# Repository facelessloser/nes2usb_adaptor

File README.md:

# nes2usb_adaptor
NES to USB adaptor

Blog post - https://facelesstech.wordpress.com/2017/03/26/nes-to-usb-adaptor-fail/
Youtube - https://youtu.be/qgFyICQwugc

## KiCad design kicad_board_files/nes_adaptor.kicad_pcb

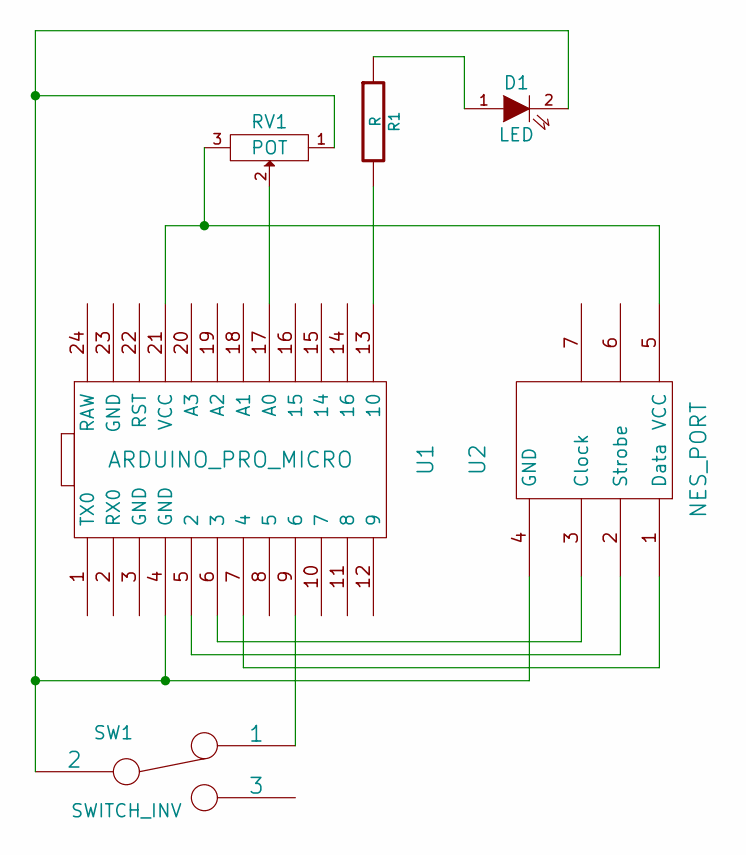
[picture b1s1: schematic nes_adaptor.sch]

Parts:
D1: LED
R1: R
RV1: POT
SW1: SWITCH_INV
U1: ARDUINO_PRO_MICRO
U2: NES_PORT

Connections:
unnamed: U1.6 (3), U2.3 (Clock)
unnamed: RV1.2, U1.17 (A0)
unnamed: SW1.1, U1.9 (6)
unnamed: U1.5 (2), U2.2 (Strobe)
unnamed: U1.7 (4), U2.1 (Data)
unnamed: D1.1 (A), R1.1
unnamed: R1.2, U1.13 (10)
unnamed: RV1.3, U1.21 (VCC), U2.5 (VCC)
unnamed: D1.2 (K), RV1.1, SW1.2, U1.4 (GND), U2.4 (GND)

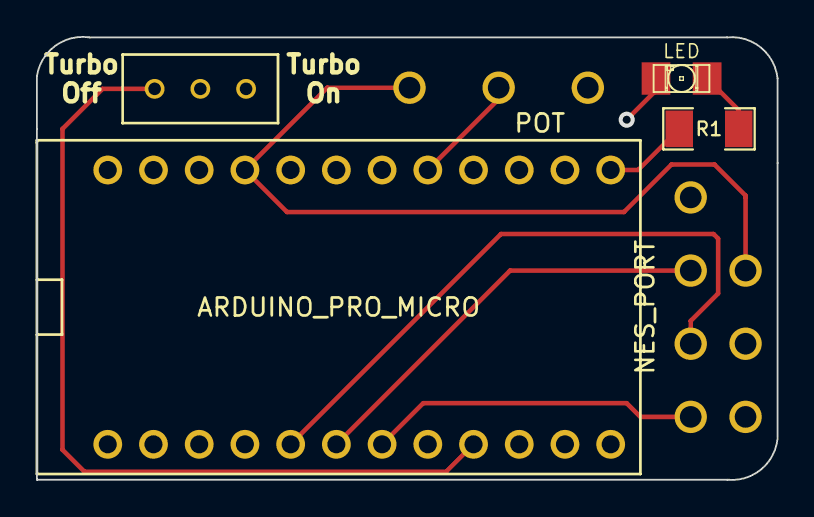
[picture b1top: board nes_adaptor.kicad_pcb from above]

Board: 2 copper layers, 41.1 x 24.6 mm, 7 parts (0 on the bottom side), 9 nets.

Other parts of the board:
VAL: OSH_final_silks_back

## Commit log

2017-03-15 kicad board files
2017-03-16 arduino sketches
2017-03-16 added led code and fixed the pot
2018-03-17 added links
